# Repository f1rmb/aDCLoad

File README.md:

Arduino Programmable Constant Current Power Resistance Load
===========================================================

This is all of the code, datasheets and design files for [my instructable](http://www.instructables.com/id/Arduino-Programmable-Constant-Current-Power-Resist/ "Arduino Programmable Constant Current Power Resistance Load") 

* Arduino - It contains the Arduino code that we will be talking about here, within the dummy load folder. It also contains all of the 3rd party libraries I have used.
* Datasheets - It contains all of the datasheets for the major components used within the project.
* DesignSpark - I have used the opensource schematic and PCB design software for this project, its a fantastic free tool that has no limitations and I find it easier to uses than Eagle - http://www.rs-online.com/designspark/electronics/eng/page/designspark-pcb-home-page The rev 1 folder contains all of my initial designs, please don't use this as there are 2 or 3 errors in the footprints plus I have completely revised the layout for rev 2, please only use these files. the gerber files are in there should you wish to have your own board done. See the next step for more information on this.
* LTSpice - This contains all of the LtSpice files from simulating the operation of the MOSFET.

Please checkout my instructable as it describes all of this code and the operation of the dummy load.

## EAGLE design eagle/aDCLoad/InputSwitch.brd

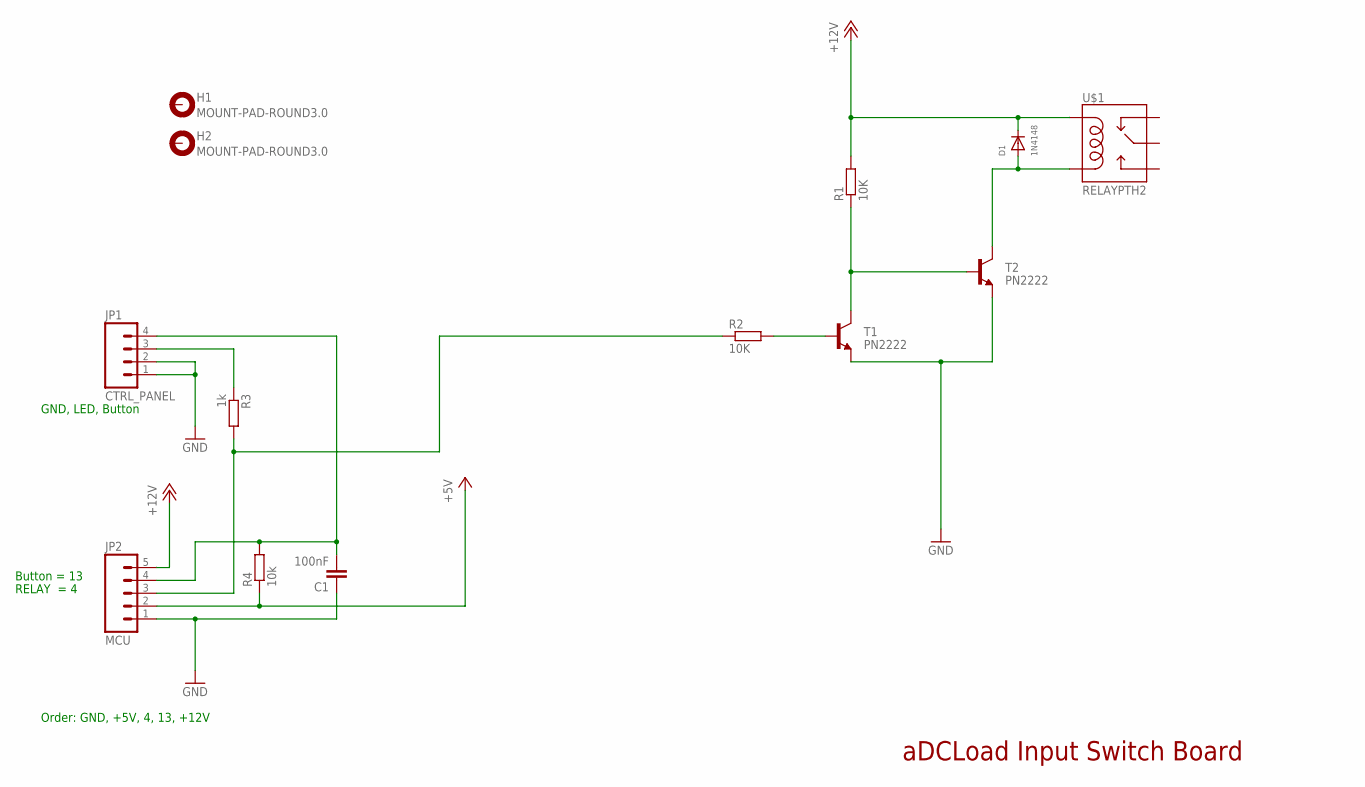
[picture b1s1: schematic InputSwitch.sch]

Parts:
C1: 100nF; C0805
D1: 1N4148; SOD-123
H1, H2: MOUNT-PAD-ROUND3.0; 3,0-PAD
JP1: CTRL_PANEL; 1X04
JP2: MCU; 1X05
R1, R2: 10K; R0805
R3: 1k; R0805
R4: 10k; R0805
T1, T2: PN2222; SOT23-3
U$1: RELAYPTH2; RELAY-T9A

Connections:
+5V: JP2.2, R4.1
+12V: D1.C, JP2.5, R1.2, U$1.COIL1
BTN: C1.2, JP1.4, JP2.4, R4.2
GND: C1.1, JP1.1, JP1.2, JP2.1, T1.2 (E), T2.2 (E)
unnamed: R2.2, T1.1 (B)
unnamed: R1.1, T1.3 (C), T2.1 (B)
unnamed: D1.A, T2.3 (C), U$1.COIL2
unnamed: JP2.3, R2.1, R3.2
RL_LED: JP1.3, R3.1

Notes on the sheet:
Button = 13
RELAY = 4
Order: GND, +5V, 4, 13, +12V
GND, LED, Button
aDCLoad Input Switch Board

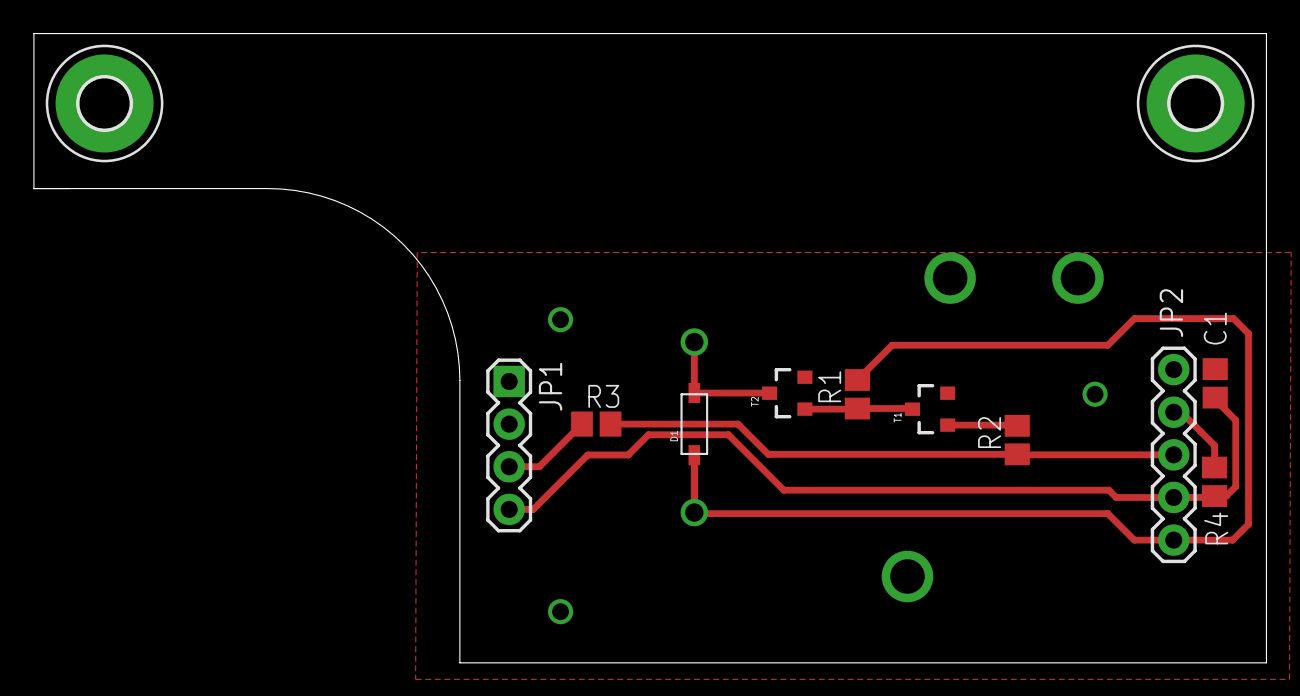
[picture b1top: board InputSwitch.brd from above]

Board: 2 copper layers, 73.5 x 37.5 mm, 13 parts (1 on the bottom side), 9 nets.

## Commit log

2014-10-20 Import aDCLoad, the Arduino controlled Constant Current DC Load.
2014-10-20 Add licences
2014-10-28 Add Doxygen comments.
2014-10-28 Import HTML documentation.
2014-10-28 Small tweaking, comments.
2014-10-28 Add doxygen's doc for private members.
2014-11-18 Documentation Update.
2014-11-18 Big update, max factorization, big cleanup.
2014-11-18 More documentation
2014-11-18 More documentation.
2014-12-04 Log of cleanup, documentation (doxy) added, logging rate fixup. First flash on real leonardo chip.
2014-12-04 Add personal doxygen css.
2014-12-06 Fix stupid button pin checking.
2014-12-06 Update doc.
2014-12-06 Use 8 pins for LCD since it's already wired (original code use 4 bits mode).
2014-12-06 Add 192W support.
2014-12-21 Implement calibration, values are stored into EEPROM. Update documentation. Code is running on my finaly built DC Load hardware, without bootloader due to flash free space.
2014-12-21 Update doc
2014-12-21 Update/cleanup calibration file
2014-12-23 Add over-temperature feature. Slow down display update rate. Ready for release this final version (documentation needs to be finished).
2014-12-29 Add voltage drop calibration ':CAL:VD:'. Update fanspeed DAC values. Don't catch OCP while calibrating. Updata malefile for fuses, flash and calibrations. Optimize EEPROM calibration backup/restore.
2014-12-30 Calibration documentations
2014-12-31 Doc update/adding.
2015-01-06 Documentation is done.
2015-01-06 Add calibration spreadsheet Excel format.
2015-01-06 Small documentation tweak
2015-01-06 Add firmware
2015-01-06 modify burn stage
2015-01-06 Documentation bump
2015-01-06 No more need that _setValue() declared as template. Update Doc
2015-01-06 New logo. Improve Latex/PDF outputs.
2015-01-08 New bin.
2015-01-08 Added tag RELEASE-2_4-08012015 for changeset e57eec727165
2015-01-10 Add Pulse Transient Time feature. Doc updated.
2015-01-10 Add Pulse Transient Time feature. Use TimerThree. Switch TimerOne version to PJRC one: https://www.pjrc.com/teensy/td_libs_TimerOne.html. Doc also updated.
2015-01-10 Update Makefile for TimerThree lib usage. New HEX.
2015-03-29 Add two mosfets and input relay support
2015-03-29 Add Eagle files for input switch board
2015-04-01 Fix fuses flash/documentation. Add F1JKY calibration values. Rebuild html/latex/mdf docs.

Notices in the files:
parts and their libraries:
SparkFun-Electromechanical: Licensing: Creative Commons ShareAlike 4.0 International - https://creativecommons.org/licenses/by-sa/4.0
